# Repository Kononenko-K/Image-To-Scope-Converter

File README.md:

# Image-To-Scope-Converter
Raster oscilloscope image generator from an arbitrary bitmap file.
<br/>

## Overview
The idea behind this project is based on the fact that rapid signal transitions are almost imperceptible on a CRT. Thus, if we make a signal jump with a very short rise/fall time from point A to point B, there will be no visible trace of movement on the display. Here, I use the MCU's DAC to generate horizontal and vertical scan signals, and an open-drain GPIO output to create the sharpest possible edge by shorting the DAC output to ground (which is not ideal, but the DAC's output impedance is relatively high anyway). This allows to return the dot on the screen to the zero position when the pixel is white, enabling the display of a raster image on any 2-channel CRT oscilloscope in XY mode without modifying its circuitry for brightness modulation.

## [Hardware](Hardware)

The board features an STM32F405 series MCU, USB-UART converter, USB Type-C connector, negative voltage generator, and a wideband 2-channel operational amplifier. [KiCad project files](/Hardware/PCB) and [PDF documentation](/Hardware/PCB/project.pdf) are avaliable. For correct operation, DACx and PWMx outputs should both be connected to the corresponding Ax pins.

## [Firmware](Firmware)
The firmware is configured to work with a 1 MBd USART speed, 256×256 image resolution, and adjustable frame rate. The MCU receives an 8192-byte array representing XBM-format images with 1 bit per pixel encoding. The frame rate can be adjusted using the button connected to the PB1 pin. A test image is included in the firmware and can be found in [test_im.h](/Firmware/Core/Src/test_im.h). It is displayed immediately after power-on until another image is loaded via UART.
The project is developed using STM32CubeIDE with HAL.

## [Software](Software)

I developed a Python PyQt6 script for the project GUI that generates properly formatted data from arbitrary images. Here are the [source code](/Software/ui.py) and [requirements](/Software/requirements.txt).

## [Enclosure](/Hardware/Enclosure)

STL files for the [case](/Hardware/Enclosure/1.stl) and its [cover](/Hardware/Enclosure/2.stl) for 3D printing.

## License
- The **Software** and **Firmware** in this project are licensed under the [MIT License](/Firmware/LICENSE), with the exception of portions of the firmware code that are copyrighted by STMicroelectronics; such portions are subject to the original licensing terms provided by STMicroelectronics.
- The **Hardware** in this project is licensed under the [CERN Open Hardware Licence Permissive (CERN OHL-P)](/Hardware/LICENSE).

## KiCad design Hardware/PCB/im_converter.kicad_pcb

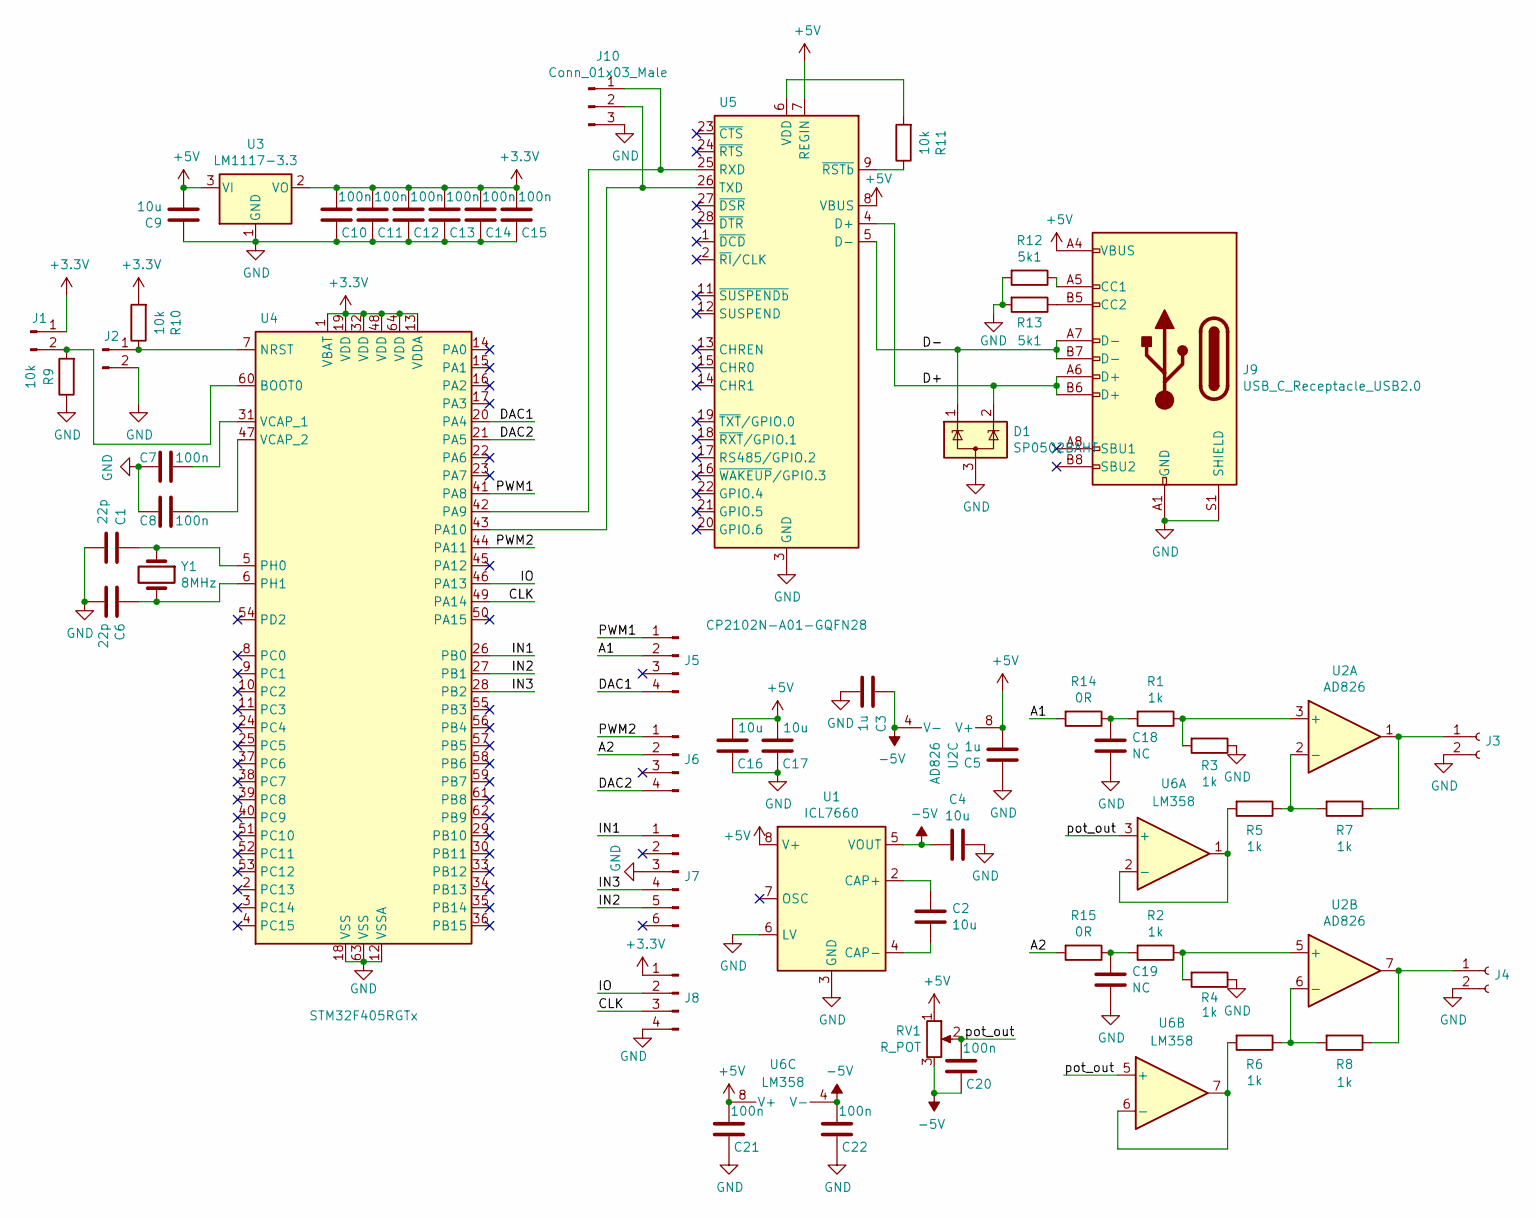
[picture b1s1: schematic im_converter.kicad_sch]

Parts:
C1, C6: 22p; C_1206_3216Metric_Pad1.33x1.80mm_HandSolder
C2, C4, C9, C16, C17: 10u; C_1206_3216Metric_Pad1.33x1.80mm_HandSolder
C3, C5: 1u; C_1206_3216Metric_Pad1.33x1.80mm_HandSolder
C7, C8, C10, C11, C12, C13, C14, C15, C20, C21, C22: 100n; C_0603_1608Metric_Pad1.08x0.95mm_HandSolder
C18, C19: NC; C_1206_3216Metric_Pad1.33x1.80mm_HandSolder
D1: SP0502BAHT; SOT-23
J1, J2: Conn_01x02_Male; PinHeader_1x02_P2.54mm_Vertical
J3, J4: Conn_01x02_Female; PinSocket_1x03_P2.54mm_Vertical
J5, J6: Conn_01x04_Male; PinHeader_2x02_P2.54mm_Vertical
J7: Conn_01x06_Male; PinHeader_2x03_P2.54mm_Vertical
J8: Conn_01x04_Male; PinHeader_1x04_P2.54mm_Vertical
J9: USB_C_Receptacle_USB2.0; USB_C_Receptacle_Palconn_UTC16-G
J10: Conn_01x03_Male; PinHeader_1x03_P2.54mm_Vertical
R1, R2, R3, R4, R5, R6, R7, R8: 1k; R_1206_3216Metric_Pad1.30x1.75mm_HandSolder
R9, R10: 10k; R_1206_3216Metric_Pad1.30x1.75mm_HandSolder
R11: 10k; R_0603_1608Metric_Pad0.98x0.95mm_HandSolder
R12, R13: 5k1; R_0603_1608Metric_Pad0.98x0.95mm_HandSolder
R14, R15: 0R; R_1206_3216Metric_Pad1.30x1.75mm_HandSolder
RV1: R_POT; Potentiometer_Bourns_3296W_Vertical
U1: ICL7660; SOIC-8_3.9x4.9mm_P1.27mm
U2: AD826; SOIC-8_3.9x4.9mm_P1.27mm
U3: LM1117-3.3; SOT-223-3_TabPin2
U4: STM32F405RGTx; LQFP-64_10x10mm_P0.5mm
U5: CP2102N-A01-GQFN28; QFN-28-1EP_5x5mm_P0.5mm_EP3.35x3.35mm
U6: LM358; SOIC-8_3.9x4.9mm_P1.27mm
Y1: 8MHz; Crystal_SMD_HC49-SD

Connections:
+3V3: C10.2, C11.2, C12.2, C13.2, C14.2, C15.2, J1.1, J8.1, R10.2, U3.2 (VO), U4.1 (VBAT), U4.13 (VDDA), U4.19 (VDD), U4.32 (VDD), U4.48 (VDD), U4.64 (VDD)
+5V: C5.2, C9.2, C16.2, C17.2, C21.2, J9.A4 (VBUS), J9.A9 (VBUS), J9.B4 (VBUS), J9.B9 (VBUS), RV1.1, U1.8 (V+), U2.8 (V+), U3.3 (VI), U5.7 (REGIN), U5.8 (VBUS), U6.8 (V+)
-5V: C3.1, C4.2, C20.1, C22.2, RV1.3, U1.5 (VOUT), U2.4 (V-), U6.4 (V-)
/A1: J5.2, R14.2
/A2: J6.2, R15.2
/CLK: J8.3, U4.49 (PA14)
/D+: D1.2 (K), J9.A6 (D+), J9.B6 (D+), U5.4 (D+)
/D-: D1.1 (K), J9.A7 (D-), J9.B7 (D-), U5.5 (D-)
/DAC1: J5.4, U4.20 (PA4)
/DAC2: J6.4, U4.21 (PA5)
/IN1: J7.1, U4.26 (PB0)
/IN2: J7.5, U4.27 (PB1)
/IN3: J7.4, U4.28 (PB2)
/IO: J8.2, U4.46 (PA13)
/PWM1: J5.1, U4.41 (PA8)
/PWM2: J6.1, U4.44 (PA11)
/pot_out: C20.2, RV1.2, U6.3 (+), U6.5 (+)
GND: C1.2, C3.2, C4.1, C5.1, C6.2, C7.2, C8.2, C9.1, C10.1, C11.1, C12.1, C13.1, C14.1, C15.1, C16.1, C17.1, C18.2, C19.2, C21.1, C22.1, D1.3 (A), J2.2, J3.2, J4.2, J7.3, J8.4, J9.A1 (GND), J9.A12 (GND), J9.B1 (GND), J9.B12 (GND), J9.S1 (SHIELD), J10.3, R3.1, R4.1, R9.1, R12.2, R13.2, U1.3 (GND), U1.6 (LV), U3.1 (GND), U4.12 (VSSA), U4.18 (VSS), U4.63 (VSS), U5.3 (GND), U5.29 (GND)
unnamed: C1.1, U4.5 (PH0), Y1.1
unnamed: C2.1, U1.2 (CAP+)
unnamed: C2.2, U1.4 (CAP-)
unnamed: C6.1, U4.6 (PH1), Y1.2
unnamed: C7.1, U4.31 (VCAP_1)
unnamed: C8.1, U4.47 (VCAP_2)
unnamed: C18.1, R1.2, R14.1
unnamed: C19.1, R2.2, R15.1
unnamed: J1.2, R9.2, U4.60 (BOOT0)
unnamed: J2.1, R10.1, U4.7 (NRST)
unnamed: J3.1, R7.1, U2.1
unnamed: J4.1, R8.1, U2.7
unnamed: J9.A5 (CC1), R12.1
unnamed: J9.B5 (CC2), R13.1
unnamed: J10.1, U4.42 (PA9), U5.25 (RXD)
unnamed: J10.2, U4.43 (PA10), U5.26 (TXD)
unnamed: R1.1, R3.2, U2.3 (+)
unnamed: R2.1, R4.2, U2.5 (+)
unnamed: R5.1, R7.2, U2.2 (-)
unnamed: R5.2, U6.1, U6.2 (-)
unnamed: R6.1, R8.2, U2.6 (-)
unnamed: R6.2, U6.6 (-), U6.7
unnamed: R11.1, U5.9 (~RSTb)
unnamed: R11.2, U5.6 (VDD)

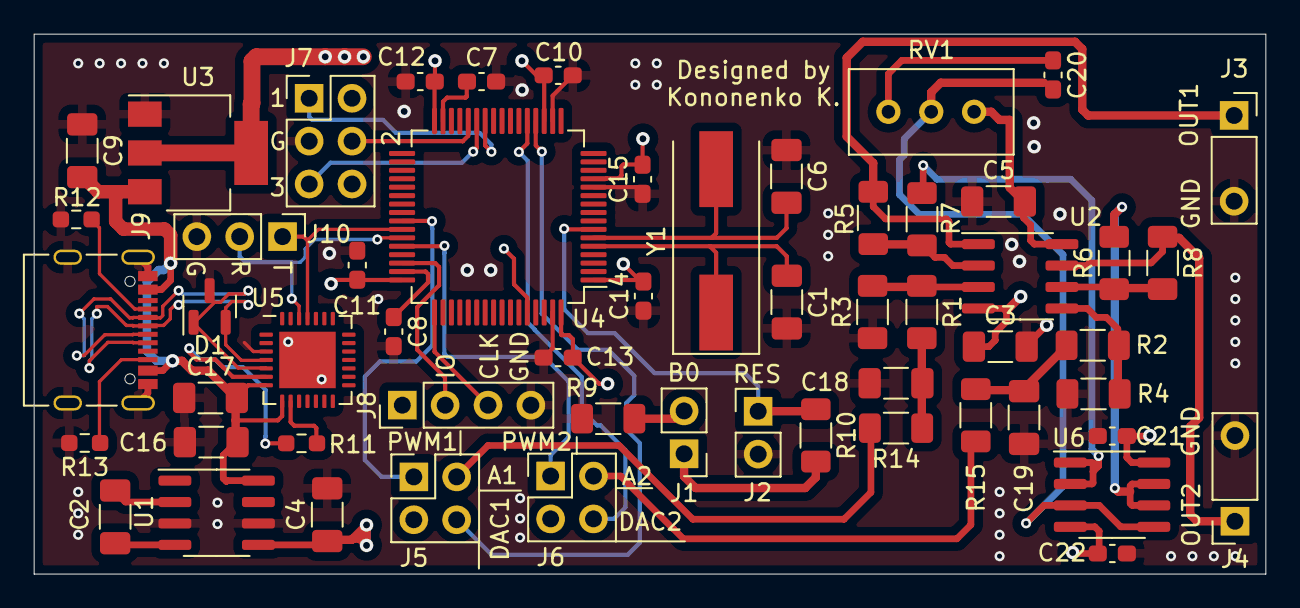
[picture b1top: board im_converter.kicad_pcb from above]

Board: 4 copper layers, 73.0 x 32.0 mm, 56 parts (0 on the bottom side), 42 nets.

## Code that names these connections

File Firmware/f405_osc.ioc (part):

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Mcu.Name=STM32F405RGTx
Mcu.Package=LQFP64
Mcu.UserName=STM32F405RGTx
PA10.Mode=Asynchronous
PA10.Signal=USART1_RX
PA11.GPIOParameters=GPIO_Speed,GPIO_ModeDefaultOutputPP
PA11.GPIO_ModeDefaultOutputPP=GPIO_MODE_OUTPUT_OD
PA11.GPIO_Speed=GPIO_SPEED_FREQ_VERY_HIGH
PA11.Signal=GPIO_Output
PA13.Mode=Serial_Wire
PA13.Signal=SYS_JTMS-SWDIO
PA14.Mode=Serial_Wire
PA14.Signal=SYS_JTCK-SWCLK
PA4.Signal=COMP_DAC1_group
PA5.Signal=COMP_DAC2_group
PA8.GPIOParameters=GPIO_Speed,GPIO_ModeDefaultOutputPP
PA8.GPIO_ModeDefaultOutputPP=GPIO_MODE_OUTPUT_OD
PA8.GPIO_Speed=GPIO_SPEED_FREQ_VERY_HIGH
PA8.Signal=GPIO_Output
PA9.Mode=Asynchronous
PA9.Signal=USART1_TX
PB2.GPIOParameters=GPIO_PuPd
PB2.GPIO_PuPd=GPIO_PULLUP
PB2.Signal=GPIO_Input
PH0-OSC_IN.Mode=HSE-External-Oscillator
PH0-OSC_IN.Signal=RCC_OSC_IN
PH1-OSC_OUT.Mode=HSE-External-Oscillator
PH1-OSC_OUT.Signal=RCC_OSC_OUT
RCC.HSE_VALUE=8000000
RCC.SYSCLKFreq_VALUE=168000000
RCC.SYSCLKSource=RCC_SYSCLKSOURCE_PLLCLK
board=custom

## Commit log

2023-09-05 Update README.md
    -
2025-06-29 Improved project structure
2025-06-29 Fixed a broken link
2025-09-13 Updated UI application to support PyQt6
